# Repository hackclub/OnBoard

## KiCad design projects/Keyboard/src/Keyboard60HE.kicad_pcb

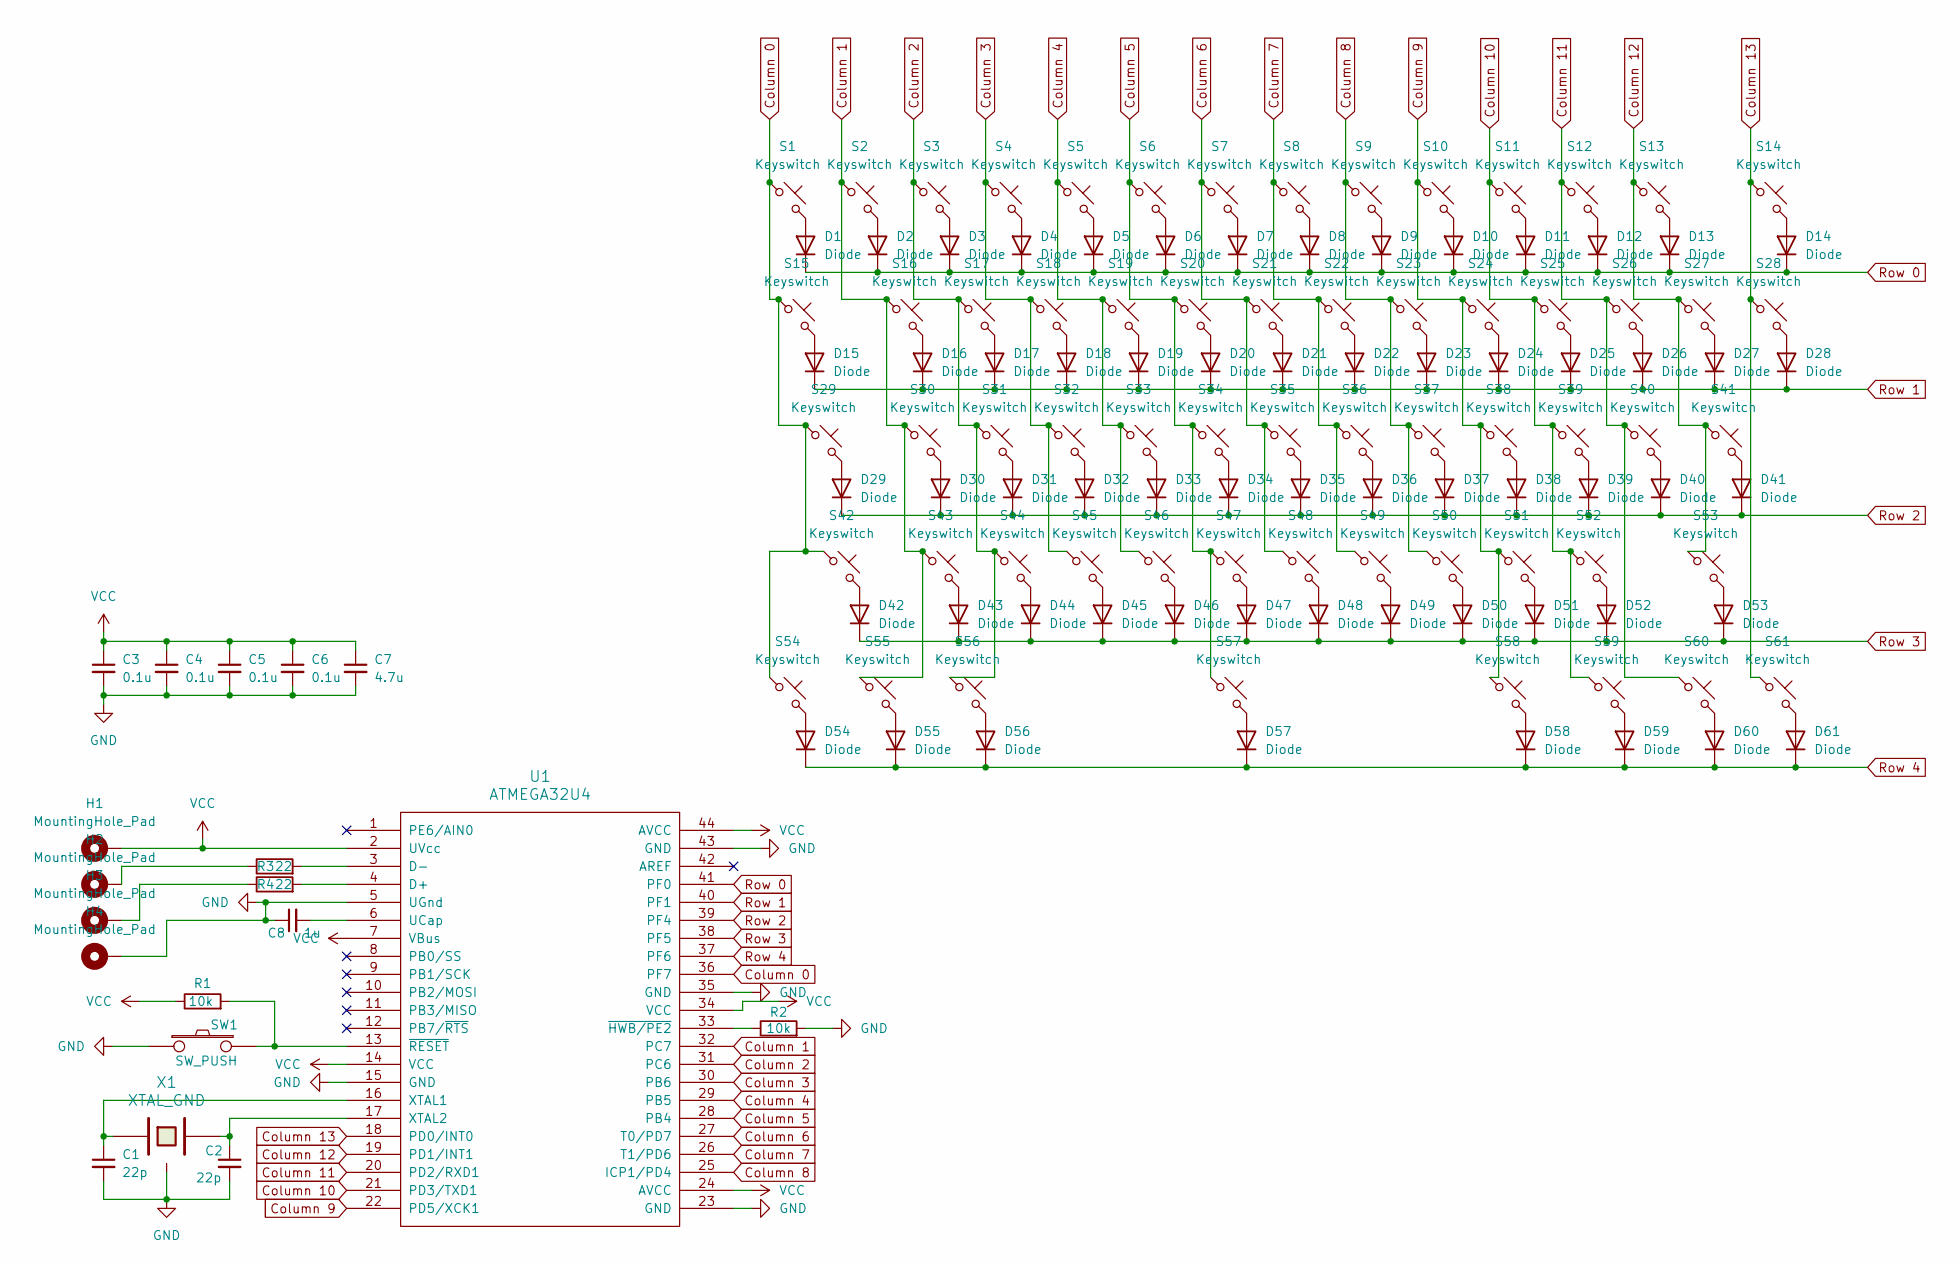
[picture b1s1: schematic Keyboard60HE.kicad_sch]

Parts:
C1, C2: 22p; C_0805_2012Metric
C3, C4, C5, C6: 0.1u; C_0805_2012Metric
C7: 4.7u; C_0805_2012Metric
C8: 1u; C_0805_2012Metric
D1, D2, D3, D4, D5, D6, D7, D8, D9, D10, D11, D12, D13, D14, D15, D16, D17, D18, D19, D20, D21, D22, D23, D24, D25, D26, D27, D28, D29, D30, D31, D32, D33, D34, D35, D36, D37, D38, D39, D40, D41, D42, D43, D44, D45, D46, D47, D48, D49, D50, D51, D52, D53, D54, D55, D56, D57, D58, D59, D60, D61: Diode; Diode_SOD-123
H1, H2, H3, H4: MountingHole_Pad; TestPoint
R1, R2: 10k; R_0805_2012Metric
R3, R4: 22; R_0805_2012Metric
S1, S2, S3, S4, S5, S6, S7, S8, S9, S10, S11, S12, S13, S16, S17, S18, S19, S20, S21, S22, S23, S24, S25, S26, S27, S30, S31, S32, S33, S34, S35, S36, S37, S38, S39, S40, S43, S44, S45, S46, S47, S48, S49, S50, S51, S52: Keyswitch; MX_PCB_1.00u
S14: Keyswitch; MX_PCB_2.00u
S15, S28: Keyswitch; MX_PCB_1.50u
S29: Keyswitch; MX_PCB_1.75u
S41, S42: Keyswitch; MX_PCB_2.25u
S53: Keyswitch; MX_PCB_2.75u
S54, S55, S56, S58, S59, S60, S61: Keyswitch; MX_PCB_1.25u
S57: Keyswitch; MX_PCB_6.25u
SW1: SW_PUSH; Button_TL3342
U1: ATMEGA32U4; TQFP-44_10x10mm_P0.8mm
X1: XTAL_GND; FA-238

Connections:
Column 0: S1.1, S15.1, S29.1, S42.1, S54.1, U1.36 (PF7)
Column 1: S2.1, S16.1, S30.1, S43.1, S55.1, U1.32 (PC7)
Column 2: S3.1, S17.1, S31.1, S44.1, S56.1, U1.31 (PC6)
Column 3: S4.1, S18.1, S32.1, S45.1, U1.30 (PB6)
Column 4: S5.1, S19.1, S33.1, S46.1, U1.29 (PB5)
Column 5: S6.1, S20.1, S34.1, S47.1, S57.1, U1.28 (PB4)
Column 6: S7.1, S21.1, S35.1, S48.1, U1.27 (T0/PD7)
Column 7: S8.1, S22.1, S36.1, S49.1, U1.26 (T1/PD6)
Column 8: S9.1, S23.1, S37.1, S50.1, U1.25 (ICP1/PD4)
Column 9: S10.1, S24.1, S38.1, S51.1, S58.1, U1.22 (PD5/XCK1)
Column 10: S11.1, S25.1, S39.1, S52.1, S59.1, U1.21 (PD3/TXD1)
Column 11: S12.1, S26.1, S40.1, S60.1, U1.20 (PD2/RXD1)
Column 12: S13.1, S27.1, S41.1, S53.1, U1.19 (PD1/INT1)
Column 13: S14.1, S28.1, S61.1, U1.18 (PD0/INT0)
GND: C1.2, C2.2, C3.2, C4.2, C5.2, C6.2, C7.2, C8.1, H4.1, R2.2, SW1.1, U1.5 (UGnd), U1.15 (GND), U1.23 (GND), U1.35 (GND), U1.43 (GND), X1.3
unnamed: D1.2 (A), S1.2
unnamed: D2.2 (A), S2.2
unnamed: D3.2 (A), S3.2
unnamed: D4.2 (A), S4.2
unnamed: D5.2 (A), S5.2
unnamed: D6.2 (A), S6.2
unnamed: D7.2 (A), S7.2
unnamed: D8.2 (A), S8.2
unnamed: D9.2 (A), S9.2
unnamed: D10.2 (A), S10.2
unnamed: D11.2 (A), S11.2
unnamed: D12.2 (A), S12.2
unnamed: D13.2 (A), S13.2
unnamed: D14.2 (A), S14.2
unnamed: D15.2 (A), S15.2
unnamed: D16.2 (A), S16.2
unnamed: D17.2 (A), S17.2
unnamed: D18.2 (A), S18.2
unnamed: D19.2 (A), S19.2
unnamed: D20.2 (A), S20.2
unnamed: D21.2 (A), S21.2
unnamed: D22.2 (A), S22.2
unnamed: D23.2 (A), S23.2
unnamed: D24.2 (A), S24.2
unnamed: D25.2 (A), S25.2
unnamed: D26.2 (A), S26.2
unnamed: D27.2 (A), S27.2
unnamed: D28.2 (A), S28.2
unnamed: D29.2 (A), S29.2
unnamed: D30.2 (A), S30.2
unnamed: D31.2 (A), S31.2
unnamed: D32.2 (A), S32.2
unnamed: D33.2 (A), S33.2
unnamed: D34.2 (A), S34.2
unnamed: D35.2 (A), S35.2
unnamed: D36.2 (A), S36.2
unnamed: D37.2 (A), S37.2
unnamed: D38.2 (A), S38.2
unnamed: D39.2 (A), S39.2
unnamed: D40.2 (A), S40.2
unnamed: D41.2 (A), S41.2
unnamed: D42.2 (A), S42.2
unnamed: D43.2 (A), S43.2
unnamed: D44.2 (A), S44.2
unnamed: D45.2 (A), S45.2
unnamed: D46.2 (A), S46.2
unnamed: D47.2 (A), S47.2
unnamed: D48.2 (A), S48.2
unnamed: D49.2 (A), S49.2
unnamed: D50.2 (A), S50.2
unnamed: D51.2 (A), S51.2
unnamed: D52.2 (A), S52.2
unnamed: D53.2 (A), S53.2
unnamed: D54.2 (A), S54.2
unnamed: D55.2 (A), S55.2
unnamed: D56.2 (A), S56.2
unnamed: D57.2 (A), S57.2
unnamed: D58.2 (A), S58.2
unnamed: D59.2 (A), S59.2
unnamed: D60.2 (A), S60.2
unnamed: D61.2 (A), S61.2
unnamed: H2.1, R3.1
unnamed: H3.1, R4.1
unnamed: R4.2, U1.4 (D+)
unnamed: R3.2, U1.3 (D-)
unnamed: C8.2, U1.6 (UCap)
unnamed: C1.1, U1.16 (XTAL1), X1.1
unnamed: C2.1, U1.17 (XTAL2), X1.2
unnamed: R2.1, U1.33 (~HWB/PE2)
unnamed: R1.2, SW1.2, U1.13 (~RESET)
Row 0: D1.1 (K), D2.1 (K), D3.1 (K), D4.1 (K), D5.1 (K), D6.1 (K), D7.1 (K), D8.1 (K), D9.1 (K), D10.1 (K), D11.1 (K), D12.1 (K), D13.1 (K), D14.1 (K), U1.41 (PF0)
Row 1: D15.1 (K), D16.1 (K), D17.1 (K), D18.1 (K), D19.1 (K), D20.1 (K), D21.1 (K), D22.1 (K), D23.1 (K), D24.1 (K), D25.1 (K), D26.1 (K), D27.1 (K), D28.1 (K), U1.40 (PF1)
Row 2: D29.1 (K), D30.1 (K), D31.1 (K), D32.1 (K), D33.1 (K), D34.1 (K), D35.1 (K), D36.1 (K), D37.1 (K), D38.1 (K), D39.1 (K), D40.1 (K), D41.1 (K), U1.39 (PF4)
Row 3: D42.1 (K), D43.1 (K), D44.1 (K), D45.1 (K), D46.1 (K), D47.1 (K), D48.1 (K), D49.1 (K), D50.1 (K), D51.1 (K), D52.1 (K), D53.1 (K), U1.38 (PF5)
Row 4: D54.1 (K), D55.1 (K), D56.1 (K), D57.1 (K), D58.1 (K), D59.1 (K), D60.1 (K), D61.1 (K), U1.37 (PF6)
VCC: C3.1, C4.1, C5.1, C6.1, C7.1, H1.1, R1.1, U1.2 (UVcc), U1.7 (VBus), U1.14 (VCC), U1.24 (AVCC), U1.34 (VCC), U1.44 (AVCC)

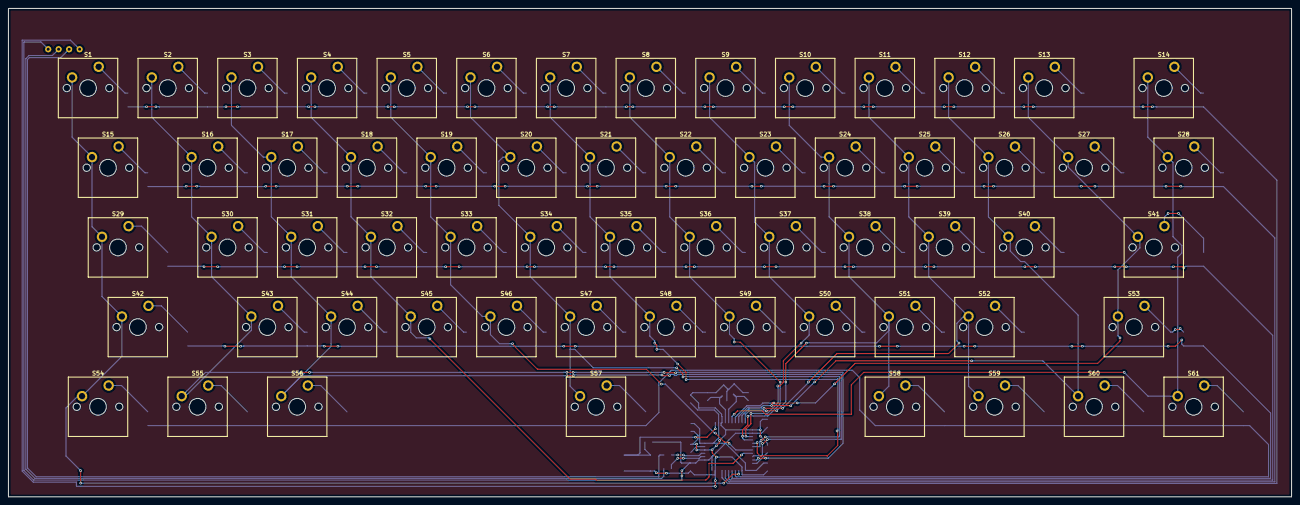
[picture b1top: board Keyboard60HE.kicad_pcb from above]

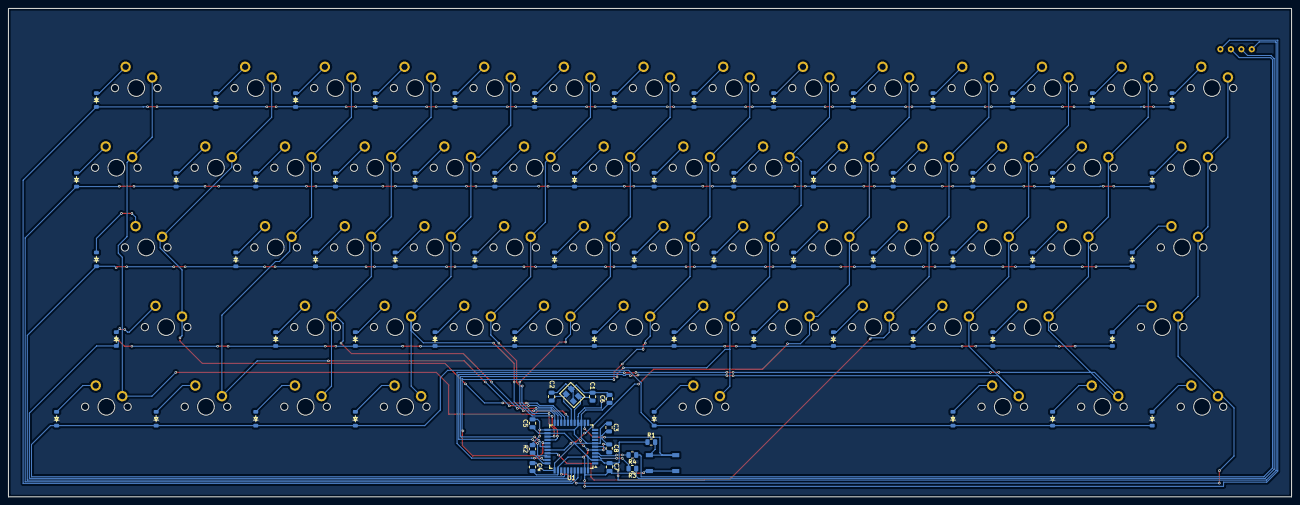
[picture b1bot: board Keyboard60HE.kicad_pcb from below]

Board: 2 copper layers, 306.8 x 116.7 mm, 141 parts (76 on the bottom side), 91 nets.

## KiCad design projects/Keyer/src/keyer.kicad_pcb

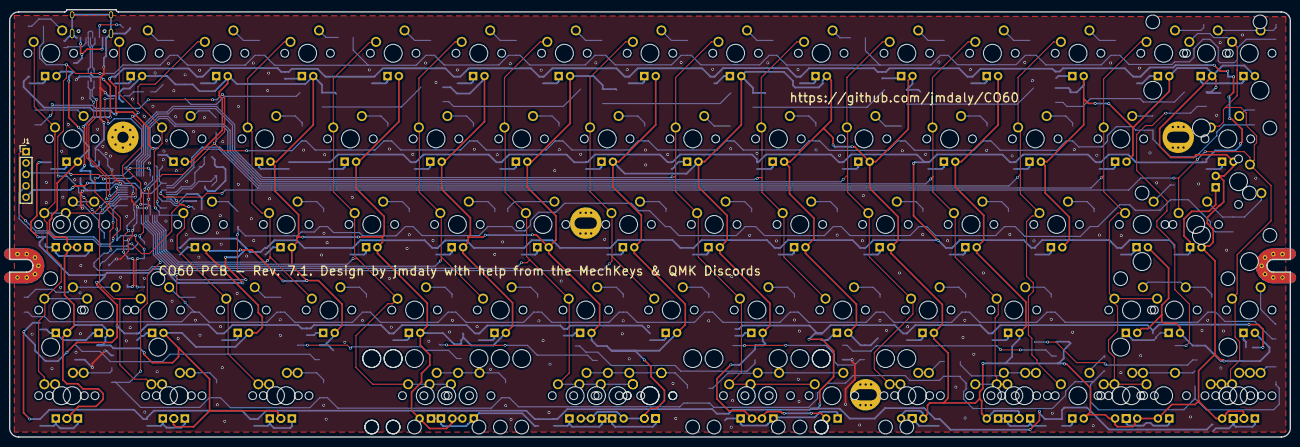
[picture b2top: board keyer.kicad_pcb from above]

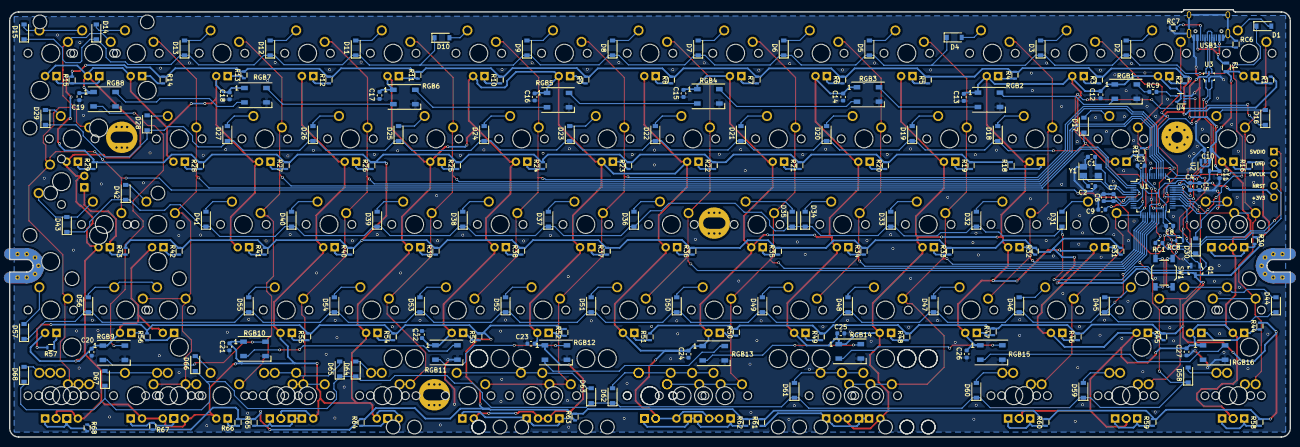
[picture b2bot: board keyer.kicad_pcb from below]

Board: 2 copper layers, 285.0 x 95.1 mm, 285 parts (193 on the bottom side), 193 nets.

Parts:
C1, C2: 30p; C_0603_1608Metric
C3, C4, C8, C9, C12, C13, C14, C15, C16, C17, C18, C19, C20, C21, C22, C23, C24, C25, C26, C27: 100n; C_0603_1608Metric
C5: 4.7u; C_0603_1608Metric
C6, C10, C11: 1u; C_0603_1608Metric
C7: 10n; C_0603_1608Metric
D1, D2, D3, D4, D5, D6, D7, D8, D9, D10, D11, D12, D13, D14, D15, D16, D17, D18, D19, D20, D21, D22, D23, D24, D25, D26, D27, D28, D29, D30, D31, D32, D33, D34, D35, D36, D37, D38, D39, D40, D41, D42, D43, D44, D45, D46, D47, D48, D49, D50, D51, D52, D53, D54, D55, D56, D57, D58, D59, D60, D61, D62, D63, D64, D65, D66, D67, D68: D_Small; D_SOD-123
F1: 500mA; R_0805
J1: Conn_01x05_Male; PinHeader_1x05_P2.54mm_Vertical
K_#0_1, K_#1, K_#2, K_#3, K_#4, K_#5, K_#6, K_#7, K_#8, K_#9: MX-1U; MXOnly-1U-FLIPPED
K_'1: MX-1U; MXOnly-1U-FLIPPED
K_,1: MX-1U; MXOnly-1U-FLIPPED
K_-1: MX-1U; MXOnly-1U-FLIPPED
K_.1: MX-1U; MXOnly-1U-FLIPPED
K_/1: MX-1U; MXOnly-1U-FLIPPED
K_;1: MX-1U; MXOnly-1U-FLIPPED
K_=1: MX-1U; MXOnly-1U-FLIPPED
K_A1: MX-1U; MXOnly-1U-FLIPPED
K_B1: MX-1U; MXOnly-1U-FLIPPED
K_BACK1: MX-2U; MXOnly-2U-FLIPPED
K_BACK2: MX-1U; MXOnly-1U-FLIPPED
K_C1: MX-1U; MXOnly-1U-FLIPPED
K_CAPS1: MX-1.75U; MXOnly-1.75U
K_CAPS2: MX-1.25U; MXOnly-1.25U-FLIPPED
K_D1: MX-1U; MXOnly-1U-FLIPPED
K_DEL1: MX-1U; MXOnly-1U-FLIPPED
K_E1: MX-1U; MXOnly-1U-FLIPPED
K_ENTER1: MX-2.25U; MXOnly-2.25U-FLIPPED
K_ESC1: MX-1U; MXOnly-1U-FLIPPED
K_F1: MX-1U; MXOnly-1U-FLIPPED
K_FN1: MX-1U; MXOnly-1U-FLIPPED
K_G1: MX-1U; MXOnly-1U-FLIPPED
K_H1: MX-1U; MXOnly-1U-FLIPPED
K_I1: MX-1U; MXOnly-1U-FLIPPED
K_ISO#1: MX-1U; MXOnly-1U-FLIPPED
K_ISOENTER1: MX-ISO; MXOnly-ISO-ROTATED-ReversedStabilizers
K_ISO\1: MX-1U; MXOnly-1U-FLIPPED
K_J1: MX-1U; MXOnly-1U-FLIPPED
K_K1: MX-1U; MXOnly-1U-FLIPPED
K_L1: MX-1U; MXOnly-1U-FLIPPED
K_LALT1: MX-1.25U; MXOnly-1.25U-FLIPPED
K_LALT2: MX-1.5U; MXOnly-1.5U
K_LCTL1: MX-1.25U; MXOnly-1.25U-FLIPPED
K_LCTL2: MX-1.5U; MXOnly-1.5U
K_LGUI1: MX-1.25U; MXOnly-1.25U-FLIPPED
K_LGUI2: MX-1U; MXOnly-1U
K_LSHIFT1: MX-2.25U; MXOnly-2.25U-FLIPPED
K_LSHIFT2: MX-1.25U; MXOnly-1.25U-FLIPPED
K_M1: MX-1U; MXOnly-1U-FLIPPED
K_N1: MX-1U; MXOnly-1U-FLIPPED
K_O1: MX-1U; MXOnly-1U-FLIPPED
K_P1: MX-1U; MXOnly-1U-FLIPPED
K_Q1: MX-1U; MXOnly-1U-FLIPPED
K_R1: MX-1U; MXOnly-1U-FLIPPED
K_RALT1: MX-1.25U; MXOnly-1.25U-FLIPPED
K_RALT3: MX-1U; MXOnly-1U
K_RCTL1: MX-1.25U; MXOnly-1.25U-FLIPPED
K_RCTL2: MX-1U; MXOnly-1U
K_RCTL3: MX-1.5U; MXOnly-1.5U
K_RFN1: MX-1.25U; MXOnly-1.25U-FLIPPED
K_RFN2, K_RFN3: MX-1U; MXOnly-1U
K_RGUI1: MX-1U; MXOnly-1U-FLIPPED
K_RMOD1: MX-1.25U; MXOnly-1.25U
K_RMOD2: MX-1U; MXOnly-1U
K_RMOD3: MX-1.5U; MXOnly-1.5U-FLIPPED
K_RSHIFT1: MX-2.75U; MXOnly-2.75U-FLIPPED
K_RSHIFT2: MX-1.75U; MXOnly-1.75U-FLIPPED
K_S1: MX-1U; MXOnly-1U-FLIPPED
K_SPACE1_1, K_SPACE3_2: MX-2.25U; MXOnly-2.25U-ReversedStabilizers
K_SPACE1_2, K_SPACE3_1: MX-2.75U; MXOnly-2.75U-FLIPPED-ReversedStabilizers
K_SPACE1_3, K_SPACE3_3: MX-2.75U; MXOnly-2.75U-ReversedStabilizers
K_SPACE2_1, K_SPACE2_5: MX-1.25U; MXOnly-1.25U-FLIPPED
K_SPACE2_2: MX-6.25U; MXOnly-6.25U-ReversedStabilizers
K_SPACE2_3: MX-7U; MXOnly-7U-ReversedStabilizers
K_SPACE2_4: MX-1.5U; MXOnly-1.5U
K_T1: MX-1U; MXOnly-1U-FLIPPED
K_TAB1: MX-1.5U; MXOnly-1.5U-FLIPPED
K_U1: MX-1U; MXOnly-1U-FLIPPED
K_V1: MX-1U; MXOnly-1U-FLIPPED
K_W1: MX-1U; MXOnly-1U-FLIPPED
K_X1: MX-1U; MXOnly-1U-FLIPPED
K_Y1: MX-1U; MXOnly-1U-FLIPPED
K_Z1: MX-1U; MXOnly-1U-FLIPPED
K_[1: MX-1U; MXOnly-1U-FLIPPED
K_\1: MX-1.5U; MXOnly-1.5U-FLIPPED
K_]1: MX-1U; MXOnly-1U-FLIPPED
Q1: FMMT493TA; SOT-23-3
R1, R2, R3, R4, R5, R6, R7, R8, R9, R10, R11, R12, R13, R14, R15, R16, R17, R18, R19, R20, R21, R22, R23, R24, R25, R26, R27, R28, R29, R30, R31, R32, R33, R34, R35, R36, R37, R38, R39, R40, R41, R42, R43, R44, R45, R46, R47, R48, R49, R50, R51, R52, R53, R54, R55, R56, R57, R58, R59, R60, R61, R62, R63, R64, R65, R66, R67, R68: 560; R_0603
RC1, RC9: 470; R_0603_1608Metric
RC6, RC7: 5.1k; R_0603
RC8: 10k; R_0603
RGB1, RGB2, RGB3, RGB4, RGB5, RGB6, RGB7, RGB8, RGB9, RGB10, RGB11, RGB12, RGB13, RGB14, RGB15, RGB16: WS2812B; LED_WS2812B_PLCC4_5.0x5.0mm_P3.2mm
SW1: SW_Push; SW_SPST_TL3342
U1: STM32F303CBTx; LQFP-48_7x7mm_Pitch0.5mm
U2: TLV70233_SOT23-5; SOT-23-5
U3: NUF2221W1T2G; SOT-363
U4: 74LVC1G34; SOT-353_SC-70-5
USB1: HRO-TYPE-C-31-M-12; HRO-TYPE-C-31-M-12-Assembly
Y1: 8MHz; Crystal_SMD_5032-4pin_5.0x3.2mm

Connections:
+3V3: C3.1, C4.1, C5.1, C6.1, C7.1, C8.1, C11.1, J1.5, SW1.1, U1.1, U1.9, U1.24, U1.36, U1.48, U2.5, U3.5
+5V: C10.1, C12.1, C13.1, C14.1, C15.1, C16.1, C17.1, C18.1, C19.1, C20.1, C21.1, C22.1, C23.1, C24.1, C25.1, C26.1, C27.1, F1.1, K_#0_1.3, K_#1.3, K_#2.3, K_#3.3, K_#4.3, K_#5.3, K_#6.3, K_#7.3, K_#8.3, K_#9.3, K_'1.3, K_,1.3, K_-1.3, K_.1.3, K_/1.3, K_;1.3, K_=1.3, K_A1.3, K_B1.3, K_BACK1.3, K_BACK2.3, K_C1.3, K_CAPS1.3, K_CAPS2.3, K_D1.3, K_DEL1.3, K_E1.3, K_ENTER1.3, K_ESC1.3, K_F1.3, K_FN1.3, K_G1.3, K_H1.3, K_I1.3, K_ISO#1.3, K_ISOENTER1.3, K_ISO\1.3, K_J1.3, K_K1.3, K_L1.3, K_LALT1.3, K_LALT2.3, K_LCTL1.3, K_LCTL2.3, K_LGUI1.3, K_LGUI2.3, K_LSHIFT1.3, K_LSHIFT2.3, K_M1.3, K_N1.3, K_O1.3, K_P1.3, K_Q1.3, K_R1.3, K_RALT1.3, K_RALT3.3, K_RCTL1.3, K_RCTL2.3, K_RCTL3.3, K_RFN1.3, K_RFN2.3, K_RFN3.3, K_RGUI1.3, K_RMOD1.3, K_RMOD2.3, K_RMOD3.3, K_RSHIFT1.3, K_RSHIFT2.3, K_S1.3, K_SPACE1_1.3, K_SPACE1_2.3, K_SPACE1_3.3, K_SPACE2_1.3, K_SPACE2_2.3, K_SPACE2_3.3, K_SPACE2_4.3, K_SPACE2_5.3, K_SPACE3_1.3, K_SPACE3_2.3, K_SPACE3_3.3, K_T1.3, K_TAB1.3, K_U1.3, K_V1.3, K_W1.3, K_X1.3, K_Y1.3, K_Z1.3, K_[1.3, K_\1.3, K_]1.3, RGB1.1, RGB2.1, RGB3.1, RGB4.1, RGB5.1, RGB6.1, RGB7.1, RGB8.1, RGB9.1, RGB10.1, RGB11.1, RGB12.1, RGB13.1, RGB14.1, RGB15.1, RGB16.1, U2.1, U2.3, U4.5
COL0: K_CAPS1.1, K_CAPS2.1, K_ESC1.1, K_LCTL1.1, K_LCTL2.1, K_LSHIFT1.1, K_LSHIFT2.1, K_TAB1.1, U1.31
COL1: K_#1.1, K_ISO\1.1, K_LGUI1.1, K_LGUI2.1, U1.30
COL2: K_#2.1, K_A1.1, K_LALT1.1, K_LALT2.1, K_Q1.1, K_Z1.1, U1.13
COL3: K_#3.1, K_S1.1, K_W1.1, K_X1.1, U1.14
COL4: K_#4.1, K_C1.1, K_D1.1, K_E1.1, K_SPACE1_1.1, K_SPACE1_2.1, K_SPACE1_3.1, U1.15
COL5: K_#5.1, K_F1.1, K_R1.1, K_V1.1, U1.16
COL6: K_#6.1, K_B1.1, K_G1.1, K_SPACE2_1.1, K_SPACE2_2.1, K_SPACE2_3.1, K_SPACE2_4.1, K_SPACE2_5.1, K_T1.1, U1.18
COL7: K_#7.1, K_H1.1, K_N1.1, K_Y1.1, U1.19
COL8: K_#8.1, K_J1.1, K_M1.1, K_SPACE3_1.1, K_SPACE3_2.1, K_SPACE3_3.1, K_U1.1, U1.38
COL9: K_#9.1, K_,1.1, K_I1.1, K_K1.1, U1.39
COL10: K_#0_1.1, K_.1.1, K_L1.1, K_O1.1, K_RALT1.1, K_RALT3.1, U1.40
COL11: K_-1.1, K_/1.1, K_;1.1, K_P1.1, K_RMOD1.1, K_RMOD2.1, K_RMOD3.1, U1.41
COL12: K_'1.1, K_=1.1, K_RGUI1.1, K_[1.1, U1.2
COL13: K_DEL1.1, K_ISO#1.1, K_RFN1.1, K_RFN2.1, K_RFN3.1, K_RSHIFT1.1, K_RSHIFT2.1, K_]1.1, U1.3
COL14: K_BACK1.1, K_BACK2.1, K_ENTER1.1, K_FN1.1, K_ISOENTER1.1, K_RCTL1.1, K_RCTL2.1, K_RCTL3.1, K_\1.1, U1.4
D_N: U1.32, U3.3
D_NI: U3.4, USB1.5, USB1.7
D_P: U1.33, U3.1
D_PI: U3.6, USB1.6, USB1.8
GND: C1.2, C2.2, C3.2, C4.2, C5.2, C6.2, C7.2, C8.2, C9.2, C10.2, C11.2, C12.2, C13.2, C14.2, C15.2, C16.2, C17.2, C18.2, C19.2, C20.2, C21.2, C22.2, C23.2, C24.2, C25.2, C26.2, C27.2, J1.2, Q1.2, RC6.1, RC7.1, RC8.2, RGB1.3, RGB2.3, RGB3.3, RGB4.3, RGB5.3, RGB6.3, RGB7.3, RGB8.3, RGB9.3, RGB10.3, RGB11.3, RGB12.3, RGB13.3, RGB14.3, RGB15.3, RGB16.3, U1.8, U1.23, U1.35, U1.47, U2.2, U3.2, U4.3, USB1.1, USB1.12, USB1.13, Y1.2, Y1.4
LEDGND: Q1.3, R1.2, R2.2, R3.2, R4.2, R5.2, R6.2, R7.2, R8.2, R9.2, R10.2, R11.2, R12.2, R13.2, R14.2, R15.2, R16.2, R17.2, R18.2, R19.2, R20.2, R21.2, R22.2, R23.2, R24.2, R25.2, R26.2, R27.2, R28.2, R29.2, R30.2, R31.2, R32.2, R33.2, R34.2, R35.2, R36.2, R37.2, R38.2, R39.2, R40.2, R41.2, R42.2, R43.2, R44.2, R45.2, R46.2, R47.2, R48.2, R49.2, R50.2, R51.2, R52.2, R53.2, R54.2, R55.2, R56.2, R57.2, R58.2, R59.2, R60.2, R61.2, R62.2, R63.2, R64.2, R65.2, R66.2, R67.2, R68.2
LEDPWM: RC1.2, U1.45
NRST: C9.1, J1.4, U1.7
unnamed: D1.2, K_ESC1.2
unnamed: D2.2, K_#1.2
unnamed: D3.2, K_#2.2
unnamed: D4.2, K_#3.2
unnamed: D5.2, K_#4.2
unnamed: D6.2, K_#5.2
unnamed: D7.2, K_#6.2
unnamed: D8.2, K_#7.2
unnamed: D9.2, K_#8.2
unnamed: D10.2, K_#9.2
unnamed: D11.2, K_#0_1.2
unnamed: D12.2, K_-1.2
unnamed: D13.2, K_=1.2
unnamed: D14.2, K_DEL1.2
unnamed: D15.2, K_BACK1.2, K_BACK2.2
unnamed: D16.2, K_TAB1.2
unnamed: D17.2, K_Q1.2
unnamed: D18.2, K_W1.2
unnamed: D19.2, K_E1.2
unnamed: D20.2, K_R1.2
unnamed: D21.2, K_T1.2
unnamed: D22.2, K_Y1.2
unnamed: D23.2, K_U1.2
unnamed: D24.2, K_I1.2
unnamed: D25.2, K_O1.2
unnamed: D26.2, K_P1.2
unnamed: D27.2, K_[1.2
unnamed: D28.2, K_]1.2
unnamed: D29.2, K_\1.2
unnamed: D30.2, K_CAPS1.2, K_CAPS2.2
unnamed: D31.2, K_A1.2
unnamed: D32.2, K_S1.2
unnamed: D33.2, K_D1.2
unnamed: D34.2, K_F1.2
unnamed: D35.2, K_G1.2
unnamed: D36.2, K_H1.2
unnamed: D37.2, K_J1.2
unnamed: D38.2, K_K1.2
unnamed: D39.2, K_L1.2
unnamed: D40.2, K_;1.2
unnamed: D41.2, K_'1.2
unnamed: D42.2, K_ISO#1.2
unnamed: D43.2, K_ENTER1.2, K_ISOENTER1.2
unnamed: D44.2, K_LSHIFT1.2, K_LSHIFT2.2
unnamed: D45.2, K_ISO\1.2
unnamed: D46.2, K_Z1.2
unnamed: D47.2, K_X1.2
unnamed: D48.2, K_C1.2
unnamed: D49.2, K_V1.2
unnamed: D50.2, K_B1.2
unnamed: D51.2, K_N1.2
unnamed: D52.2, K_M1.2
unnamed: D53.2, K_,1.2
unnamed: D54.2, K_.1.2
unnamed: D55.2, K_/1.2
unnamed: D56.2, K_RSHIFT1.2, K_RSHIFT2.2
unnamed: D57.2, K_FN1.2
unnamed: D58.2, K_LCTL1.2, K_LCTL2.2
unnamed: D59.2, K_LGUI1.2, K_LGUI2.2
unnamed: D60.2, K_LALT1.2, K_LALT2.2
unnamed: D61.2, K_SPACE1_1.2, K_SPACE1_2.2, K_SPACE1_3.2
unnamed: D62.2, K_SPACE2_1.2, K_SPACE2_2.2, K_SPACE2_3.2, K_SPACE2_4.2, K_SPACE2_5.2
unnamed: D63.2, K_SPACE3_1.2, K_SPACE3_2.2, K_SPACE3_3.2
unnamed: D64.2, K_RALT1.2, K_RALT3.2
unnamed: D65.2, K_RMOD1.2, K_RMOD2.2, K_RMOD3.2
unnamed: D66.2, K_RGUI1.2
unnamed: D67.2, K_RFN1.2, K_RFN2.2, K_RFN3.2
unnamed: D68.2, K_RCTL1.2, K_RCTL2.2, K_RCTL3.2
unnamed: K_#0_1.4, R11.1
unnamed: K_#1.4, R2.1
unnamed: K_#2.4, R3.1
unnamed: K_#3.4, R4.1
unnamed: K_#4.4, R5.1
unnamed: K_#5.4, R6.1
unnamed: K_#6.4, R7.1
unnamed: K_#7.4, R8.1
unnamed: K_#8.4, R9.1
unnamed: K_#9.4, R10.1
unnamed: K_'1.4, R41.1
unnamed: K_,1.4, R53.1
unnamed: K_-1.4, R12.1
unnamed: K_.1.4, R54.1
unnamed: K_/1.4, R55.1
unnamed: K_;1.4, R40.1
unnamed: K_=1.4, R13.1
unnamed: K_A1.4, R31.1
unnamed: K_B1.4, R50.1
unnamed: K_BACK1.4, K_BACK2.4, R15.1
unnamed: K_C1.4, R48.1
unnamed: K_CAPS1.4, K_CAPS2.4, R30.1
unnamed: K_D1.4, R33.1
unnamed: K_DEL1.4, R14.1
unnamed: K_E1.4, R19.1
unnamed: K_ENTER1.4, K_ISOENTER1.4, R43.1
unnamed: K_ESC1.4, R1.1
unnamed: K_F1.4, R34.1
unnamed: K_FN1.4, R57.1
unnamed: K_G1.4, R35.1
unnamed: K_H1.4, R36.1
unnamed: K_I1.4, R24.1
unnamed: K_ISO#1.4, R42.1
unnamed: K_ISO\1.4, R45.1
unnamed: K_J1.4, R37.1
unnamed: K_K1.4, R38.1
unnamed: K_L1.4, R39.1
unnamed: K_LALT1.4, K_LALT2.4, R60.1
unnamed: K_LCTL1.4, K_LCTL2.4, R58.1
unnamed: K_LGUI1.4, K_LGUI2.4, R59.1
unnamed: K_LSHIFT1.4, K_LSHIFT2.4, R44.1
unnamed: K_M1.4, R52.1
unnamed: K_N1.4, R51.1
unnamed: K_O1.4, R25.1
unnamed: K_P1.4, R26.1
unnamed: K_Q1.4, R17.1
unnamed: K_R1.4, R20.1
unnamed: K_RALT1.4, K_RALT3.4, R64.1
unnamed: K_RCTL1.4, K_RCTL2.4, K_RCTL3.4, R68.1
unnamed: K_RFN1.4, K_RFN2.4, K_RFN3.4, R67.1
unnamed: K_RGUI1.4, R66.1
unnamed: K_RMOD1.4, K_RMOD2.4, K_RMOD3.4, R65.1
unnamed: K_RSHIFT1.4, K_RSHIFT2.4, R56.1
unnamed: K_S1.4, R32.1
unnamed: K_SPACE1_1.4, K_SPACE1_2.4, K_SPACE1_3.4, R61.1
unnamed: K_SPACE2_1.4, K_SPACE2_2.4, K_SPACE2_3.4, K_SPACE2_4.4, K_SPACE2_5.4, R62.1
unnamed: K_SPACE3_1.4, K_SPACE3_2.4, K_SPACE3_3.4, R63.1
unnamed: K_T1.4, R21.1
unnamed: K_TAB1.4, R16.1
unnamed: K_U1.4, R23.1
unnamed: K_V1.4, R49.1
unnamed: K_W1.4, R18.1
unnamed: K_X1.4, R47.1
unnamed: K_Y1.4, R22.1
unnamed: K_Z1.4, R46.1
unnamed: K_[1.4, R27.1
unnamed: K_\1.4, R29.1
unnamed: K_]1.4, R28.1
unnamed: Q1.1, RC1.1
unnamed: RC6.2, USB1.4
unnamed: RC7.2, USB1.10
unnamed: RC8.1, SW1.2, U1.44
unnamed: RC9.2, U4.4
unnamed: RGB1.2, RGB2.4
unnamed: RGB2.2, RGB3.4
unnamed: RGB3.2, RGB4.4
unnamed: RGB4.2, RGB5.4
unnamed: RGB5.2, RGB6.4
unnamed: RGB6.2, RGB7.4
unnamed: RGB7.2, RGB8.4
unnamed: RGB8.2, RGB9.4
unnamed: RGB10.2, RGB11.4
unnamed: RGB9.2, RGB10.4
unnamed: RGB11.2, RGB12.4
unnamed: RGB12.2, RGB13.4
unnamed: RGB13.2, RGB14.4
unnamed: RGB14.2, RGB15.4
unnamed: RGB15.2, RGB16.4
OSC_IN: C1.1, U1.5, Y1.3
OSC_OUT: C2.1, U1.6, Y1.1
RGBLED: RC9.1, RGB1.4
RGBLED_3V3: U1.17, U4.2
ROW0: D1.1, D2.1, D3.1, D4.1, D5.1, D6.1, D7.1, D8.1, D9.1, D10.1, D11.1, D12.1, D13.1, D14.1, D15.1, U1.29
ROW1: D16.1, D17.1, D18.1, D19.1, D20.1, D21.1, D22.1, D23.1, D24.1, D25.1, D26.1, D27.1, D28.1, D29.1, U1.12
ROW2: D30.1, D31.1, D32.1, D33.1, D34.1, D35.1, D36.1, D37.1, D38.1, D39.1, D40.1, D41.1, D42.1, D43.1, U1.26
ROW3: D44.1, D45.1, D46.1, D47.1, D48.1, D49.1, D50.1, D51.1, D52.1, D53.1, D54.1, D55.1, D56.1, D57.1, U1.20
ROW4: D58.1, D59.1, D60.1, D61.1, D62.1, D63.1, D64.1, D65.1, D66.1, D67.1, D68.1, U1.21
SWCLK: J1.3, U1.37
SWDIO: J1.1, U1.34
VCC: F1.2, USB1.2, USB1.11

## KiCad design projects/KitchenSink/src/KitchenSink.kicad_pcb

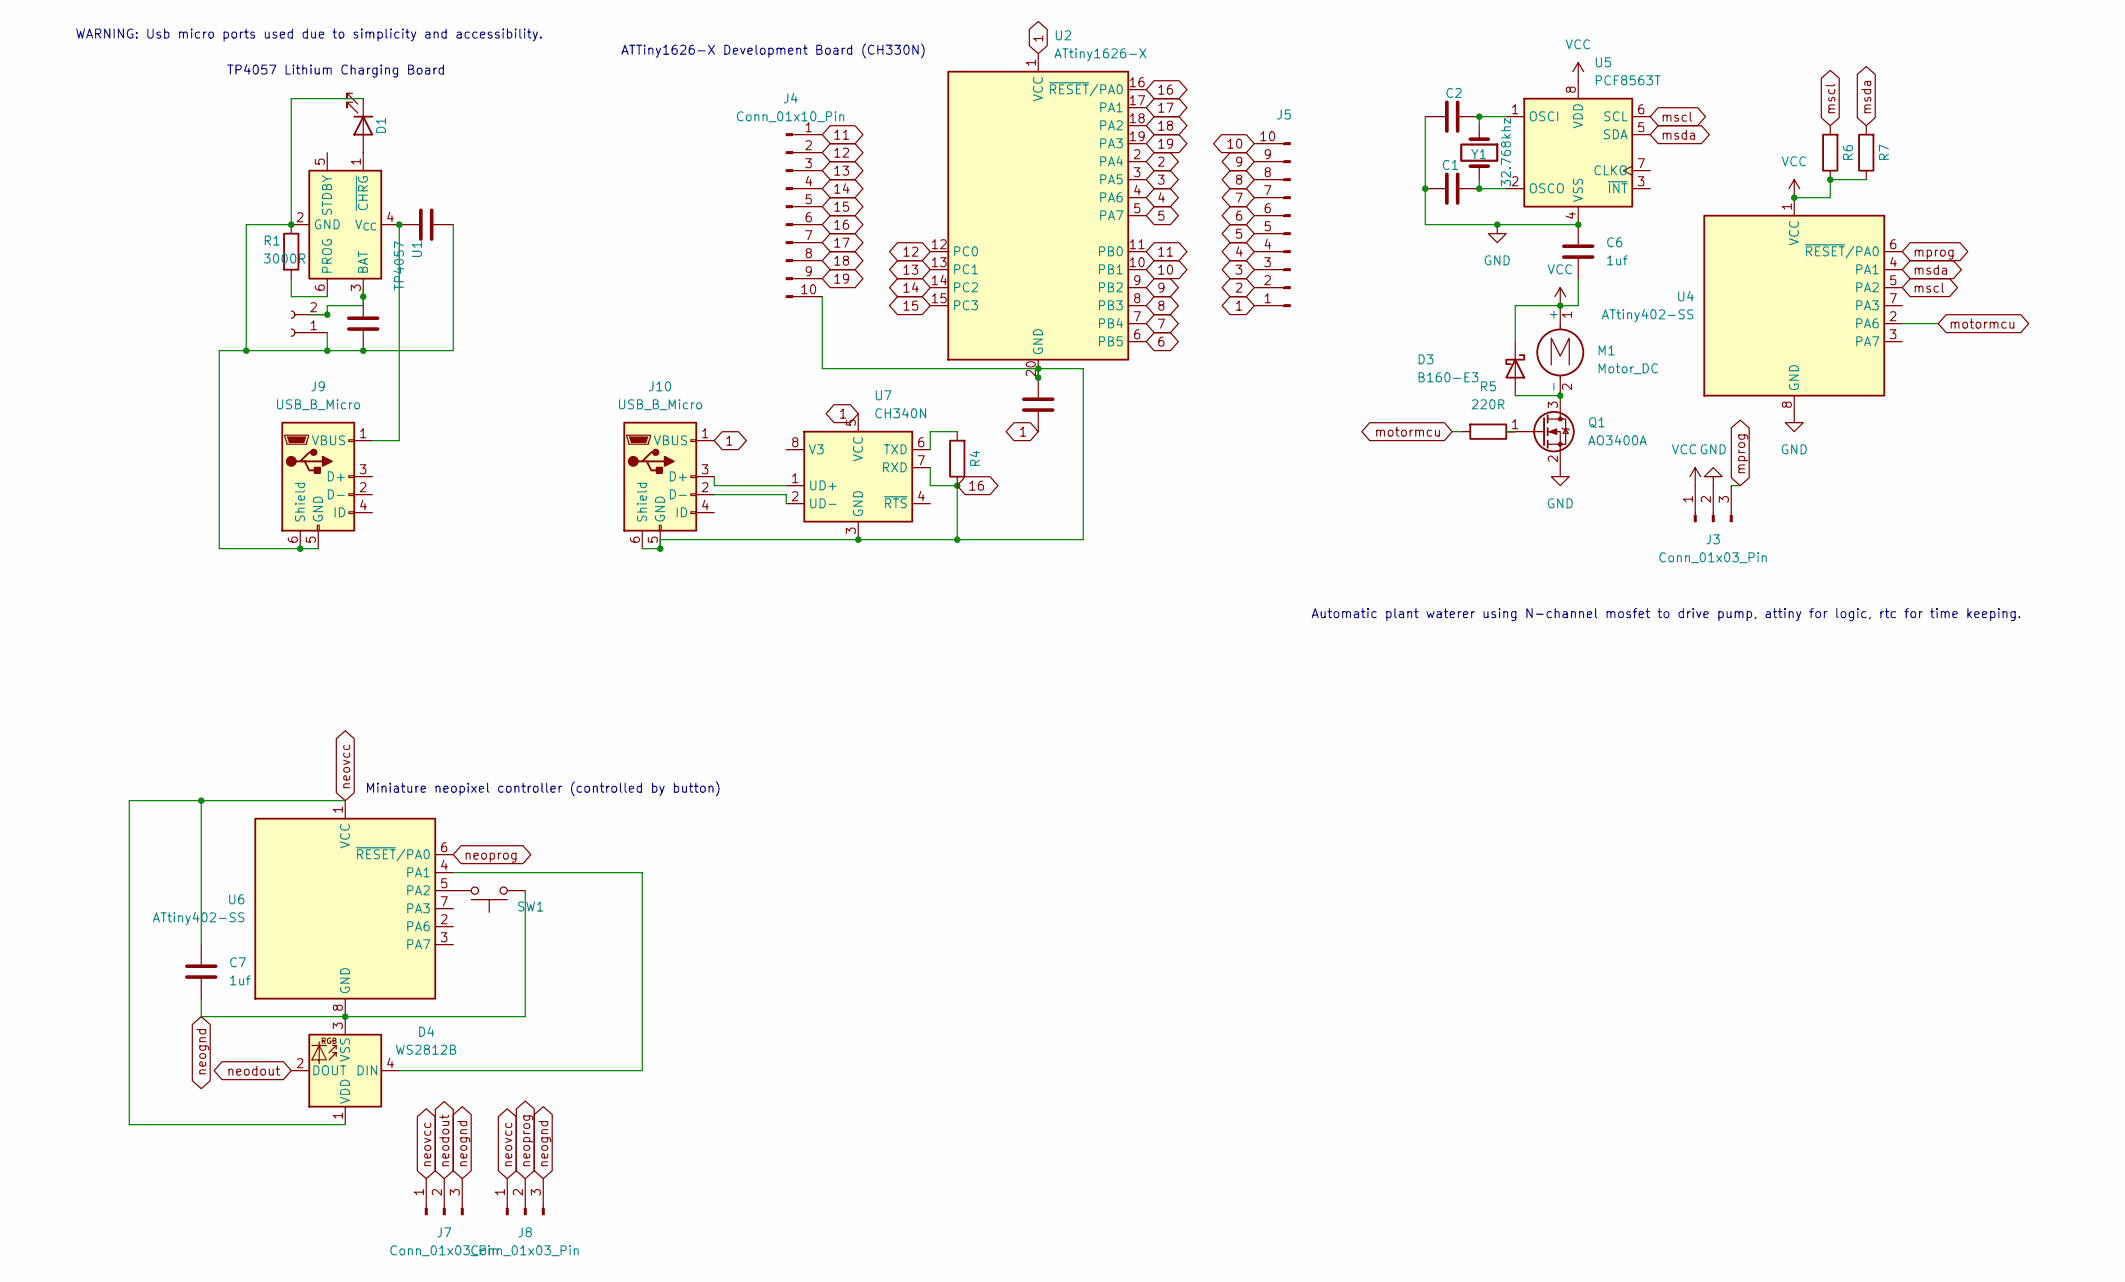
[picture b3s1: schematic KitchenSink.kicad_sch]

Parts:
C1, C2: 22pf; C_0603_1608Metric
C3, C4, C5: 1uF; C_0603_1608Metric
C6, C7: 1uf; C_0805_2012Metric
D1: LED; LED_0402_1005Metric
D3: B160-E3; D_SMA
D4: WS2812B; LED_WS2812B_PLCC4_5.0x5.0mm_P3.2mm
J2: Conn_01x02_Socket; PinHeader_1x02_P2.54mm_Vertical
J3, J7, J8: Conn_01x03_Pin; PinHeader_1x03_P2.54mm_Vertical
J4, J5: Conn_01x10_Pin; PinHeader_1x10_P2.54mm_Vertical
J9, J10: USB_B_Micro; USB_Micro-B_Molex-105017-0001
M1: Motor_DC; PinHeader_1x02_P2.54mm_Vertical
Q1: AO3400A; SOT-23
R1: 3000R; R_0402_1005Metric
R4, R6, R7: 4700R; R_0402_1005Metric
R5: 220R; R_0603_1608Metric
SW1: SW_Omron_B3FS; SW_SPST_Omron_B3FS-100xP
U1: TP4057; TSOT-23-6
U2: ATtiny1626-X; SSOP-20_5.3x7.2mm_P0.65mm
U4, U6: ATtiny402-SS; SOIC-8_3.9x4.9mm_P1.27mm
U5: PCF8563T; SOIC-8_3.9x4.9mm_P1.27mm
U7: CH340N; SOP-8_3.9x4.9mm_P1.27mm
Y1: 32.768khz; Crystal_SMD_2012-2Pin_2.0x1.2mm

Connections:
1: C5.2, J5.1, J10.1 (VBUS), U2.1 (VCC), U7.5 (VCC)
2: J5.2, U2.2 (PA4)
3: J5.3, U2.3 (PA5)
4: J5.4, U2.4 (PA6)
5: J5.5, U2.5 (PA7)
6: J5.6, U2.6 (PB5)
7: J5.7, U2.7 (PB4)
8: J5.8, U2.8 (PB3)
9: J5.9, U2.9 (PB2)
10: J5.10, U2.10 (PB1)
11: J4.1, U2.11 (PB0)
12: J4.2, U2.12 (PC0)
13: J4.3, U2.13 (PC1)
14: J4.4, U2.14 (PC2)
15: J4.5, U2.15 (PC3)
16: C5.1, J4.6, J4.10, J10.5 (GND), J10.6 (Shield), R4.1, U2.16 (~RESET/PA0), U2.20 (GND), U7.3 (GND), U7.7 (RXD)
17: J4.7, U2.17 (PA1)
18: J4.8, U2.18 (PA2)
19: J4.9, U2.19 (PA3)
GND: C1.2, C2.1, C6.1, J3.2, Q1.2 (S), U4.8 (GND), U5.4 (VSS)
unnamed: D1.2 (A), U1.1 (~CHRG)
unnamed: C3.1, C4.2, D1.1 (K), J2.1, J9.5 (GND), J9.6 (Shield), R1.1, U1.2 (GND)
unnamed: D3.2 (A), M1.2 (-), Q1.3 (D)
unnamed: D4.4 (DIN), U6.4 (PA1)
unnamed: C4.1, J2.2, U1.3 (BAT)
unnamed: C3.2, J9.1 (VBUS), U1.4 (V_{CC})
unnamed: J10.3 (D+), U7.1 (UD+)
unnamed: J10.2 (D-), U7.2 (UD-)
unnamed: Q1.1 (G), R5.1
unnamed: R1.2, U1.6 (PROG)
unnamed: C2.2, U5.1 (OSCI), Y1.1
unnamed: C1.1, U5.2 (OSCO), Y1.2
unnamed: SW1.2, U6.5 (PA2)
unnamed: R4.2, U7.6 (TXD)
VCC: C6.2, D3.1 (K), J3.1, M1.1 (+), R6.1, R7.1, U4.1 (VCC), U5.8 (VDD)
motormcu: R5.2, U4.2 (PA6)
mprog: J3.3, U4.6 (~RESET/PA0)
mscl: R6.2, U4.5 (PA2), U5.6 (SCL)
msda: R7.2, U4.4 (PA1), U5.5 (SDA)
neodout: D4.2 (DOUT), J7.2
neognd: C7.2, D4.3 (VSS), J7.3, J8.3, SW1.1, U6.8 (GND)
neoprog: J8.2, U6.6 (~RESET/PA0)
neovcc: C7.1, D4.1 (VDD), J7.1, J8.1, U6.1 (VCC)

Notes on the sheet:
Miniature neopixel controller (controlled by button)
ATTiny1626-X Development Board (CH330N)
WARNING: Usb micro ports used due to simplicity and accessibility.
TP4057 Lithium Charging Board
Automatic plant waterer using N-channel mosfet to drive pump, attiny for logic, rtc for time keeping.

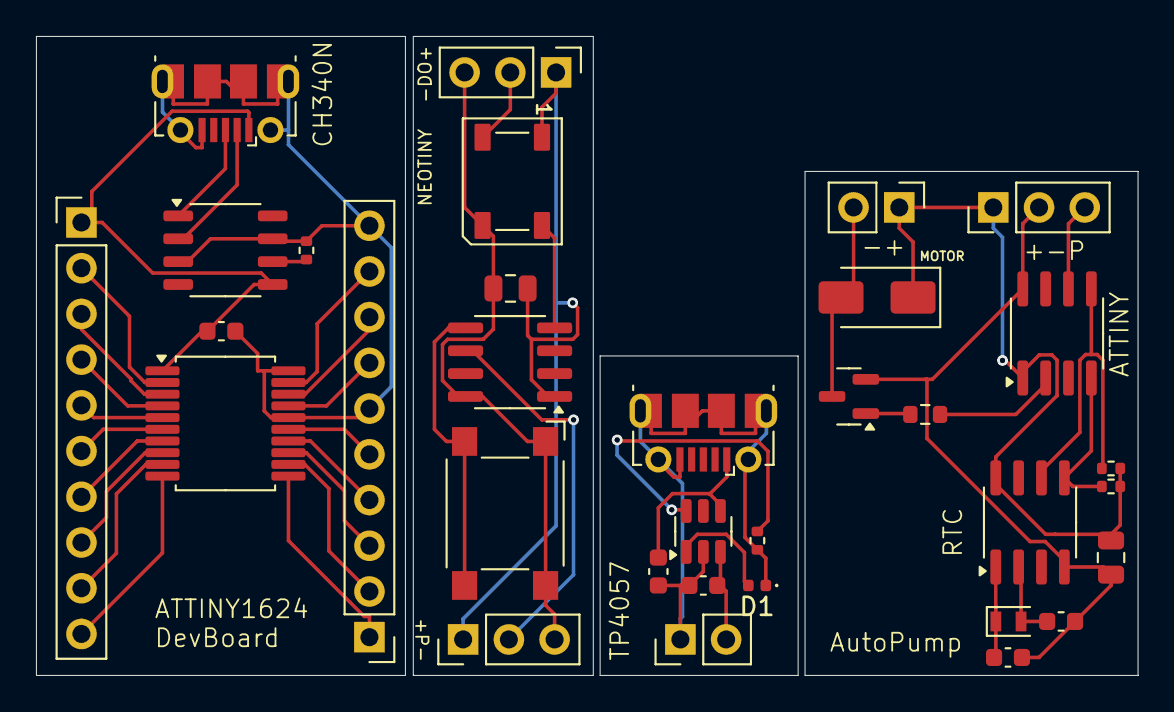
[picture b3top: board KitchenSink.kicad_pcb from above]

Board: 2 copper layers, 61.2 x 35.5 mm, 33 parts (0 on the bottom side), 43 nets.
